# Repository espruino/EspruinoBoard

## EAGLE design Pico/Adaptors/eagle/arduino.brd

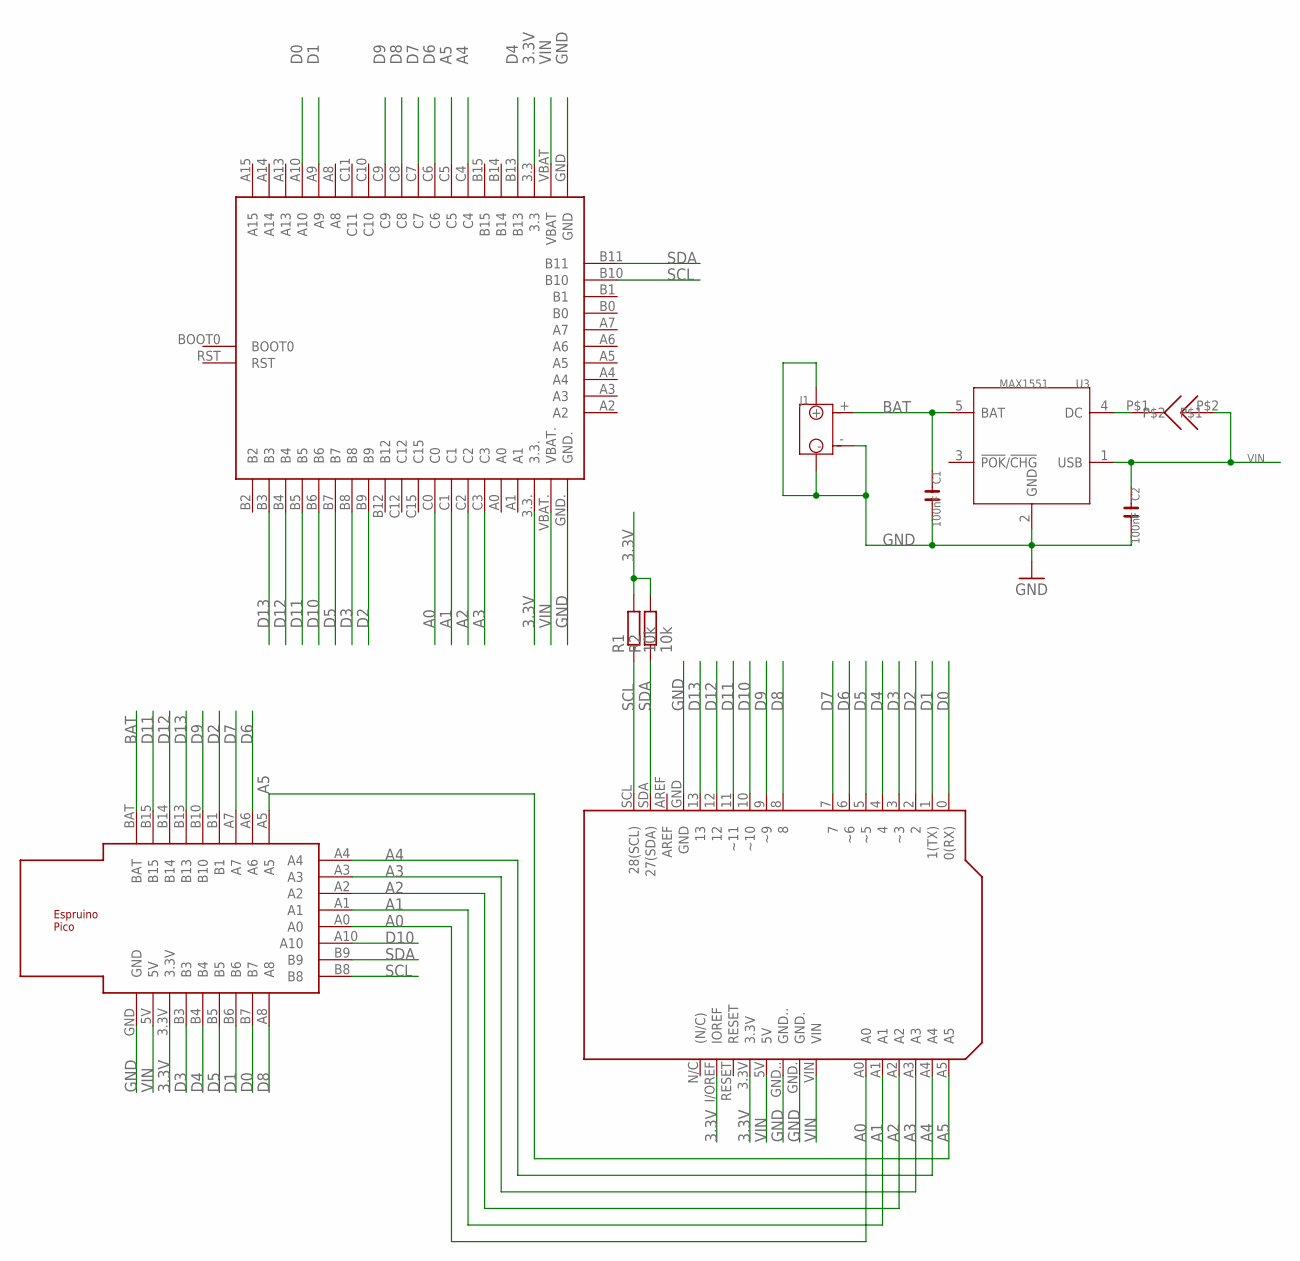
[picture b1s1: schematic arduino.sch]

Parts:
C1, C2: 100nF; C0603
J1: JST-2P-SMD-PW-3410050P1; 2P-SMD-2.0-90D
R1, R2: 10k; R0805
U3: MAX1551; SOT23-5
U$1: ESPRUINO_PICO_SMD
U$2: ARDUINO
U$3: ESPRUINO
U$4: SOLDERJUMPER

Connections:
3.3V: R1.2, R2.2, U$1.3.3V, U$2.3.3V, U$2.I/OREF (IOREF), U$3.3.3, U$3.3.3.
A0: U$1.A0, U$2.A0, U$3.C0
A1: U$1.A1, U$2.A1, U$3.C1
A2: U$1.A2, U$2.A2, U$3.C2
A3: U$1.A3, U$2.A3, U$3.C3
A4: U$1.A4, U$2.A4, U$3.C4
A5: U$1.A5, U$2.A5, U$3.C5
BAT: C1.1, J1.+, U3.5 (BAT), U$1.BAT
D0: U$1.B7, U$2.0 (0(RX)), U$3.A10
D1: U$1.B6, U$2.1 (1(TX)), U$3.A9
D2: U$1.B1, U$2.2, U$3.B9
D3: U$1.B3, U$2.3 (~3), U$3.B8
D4: U$1.B4, U$2.4, U$3.B13
D5: U$1.B5, U$2.5 (~5), U$3.B7
D6: U$1.A6, U$2.6 (~6), U$3.C6
D7: U$1.A7, U$2.7, U$3.C7
D8: U$1.A8, U$2.8, U$3.C8
D9: U$1.B10, U$2.9 (~9), U$3.C9
D10: U$1.A10, U$2.10 (~10), U$3.B6
D11: U$1.B15, U$2.11 (~11), U$3.B5
D12: U$1.B14, U$2.12, U$3.B4
D13: U$1.B13, U$2.13, U$3.B3
GND: C1.2, C2.2, J1.3, J1.4, J1.-, U3.2 (GND), U$1.GND, U$2.GND, U$2.GND., U$2.GND.., U$3.GND, U$3.GND.
unnamed: U3.4 (DC), U$4.P$1
SCL: R1.1, U$1.B8, U$2.SCL (28(SCL)), U$3.B10
SDA: R2.1, U$1.B9, U$2.SDA (27(SDA)), U$3.B11
VIN: C2.1, U3.1 (USB), U$1.5V, U$2.5V, U$2.VIN, U$3.VBAT, U$3.VBAT., U$4.P$2

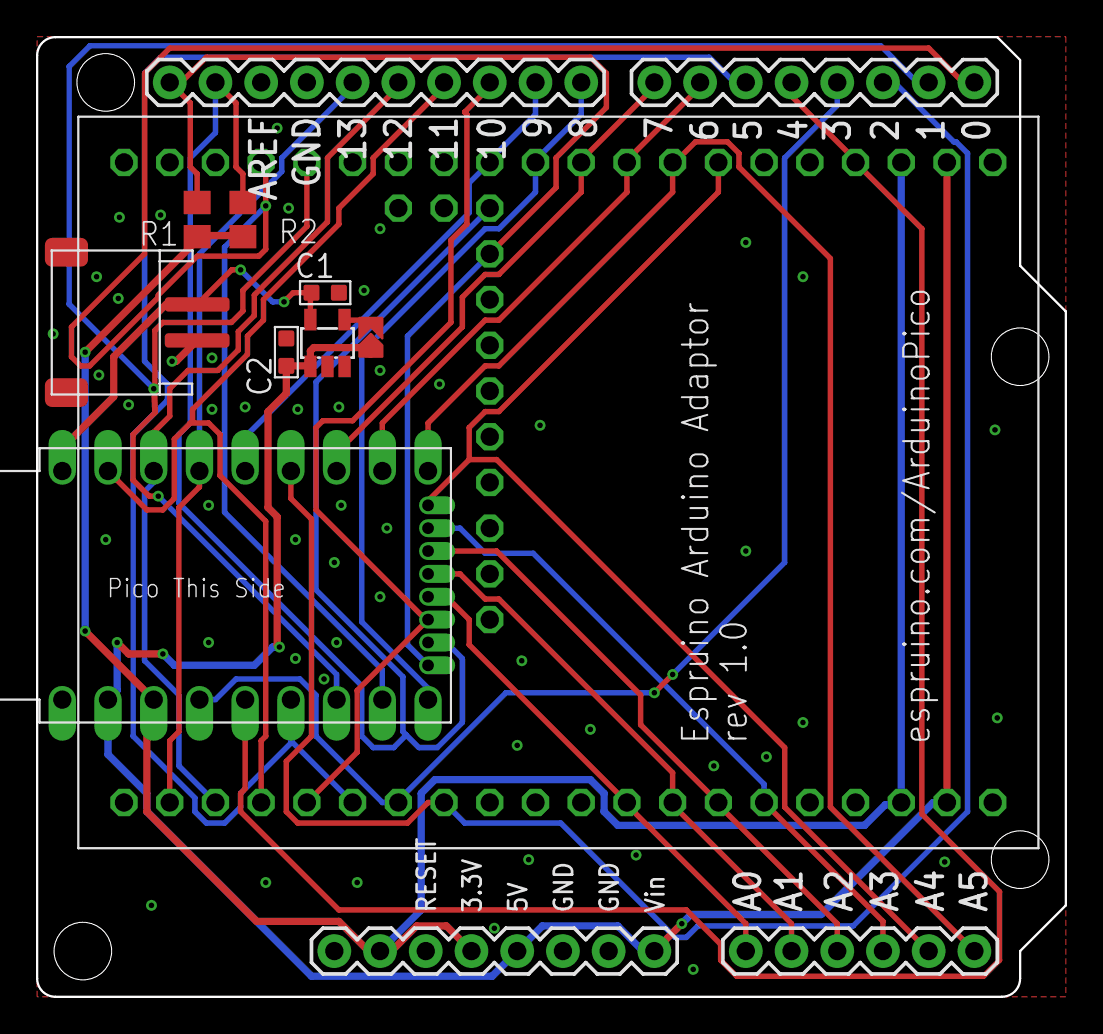
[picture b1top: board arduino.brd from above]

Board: 2 copper layers, 57.1 x 53.3 mm, 10 parts (0 on the bottom side), 27 nets.

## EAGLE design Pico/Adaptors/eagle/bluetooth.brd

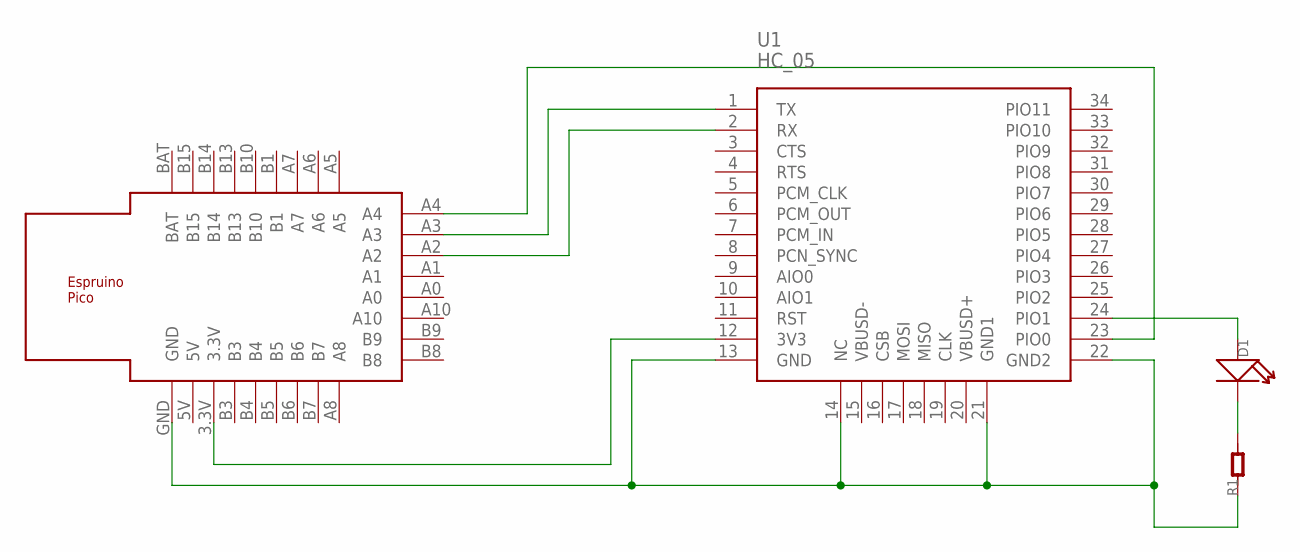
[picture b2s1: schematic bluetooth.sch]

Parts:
D1: LED; LED0603
R1: R-0603; R0603
U1: HC_05; BLUETOOTH_SMD
U$1: ESPRUINO_PICO_SMDONLY

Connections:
unnamed: U1.12 (3V3), U$1.3.3V
unnamed: R1.1, U1.13 (GND), U1.14 (NC), U1.21 (GND1), U1.22 (GND2), U$1.GND
unnamed: U1.1 (TX), U$1.A3
unnamed: U1.2 (RX), U$1.A2
unnamed: U1.23 (PIO0), U$1.A4
unnamed: D1.+, U1.24 (PIO1)
unnamed: D1.-, R1.2

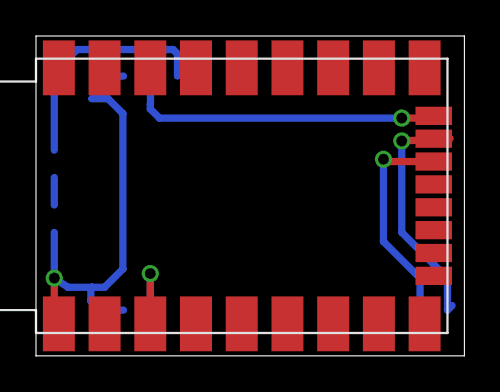
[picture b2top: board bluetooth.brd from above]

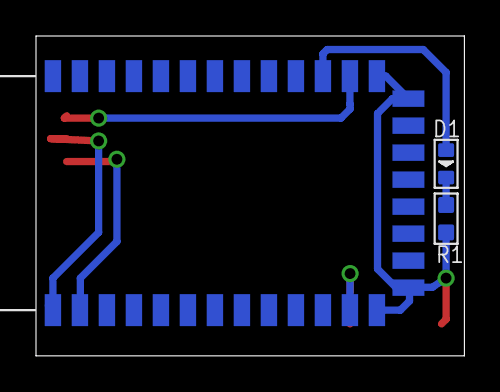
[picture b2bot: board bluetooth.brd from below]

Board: 2 copper layers, 23.8 x 17.8 mm, 4 parts (3 on the bottom side), 7 nets.

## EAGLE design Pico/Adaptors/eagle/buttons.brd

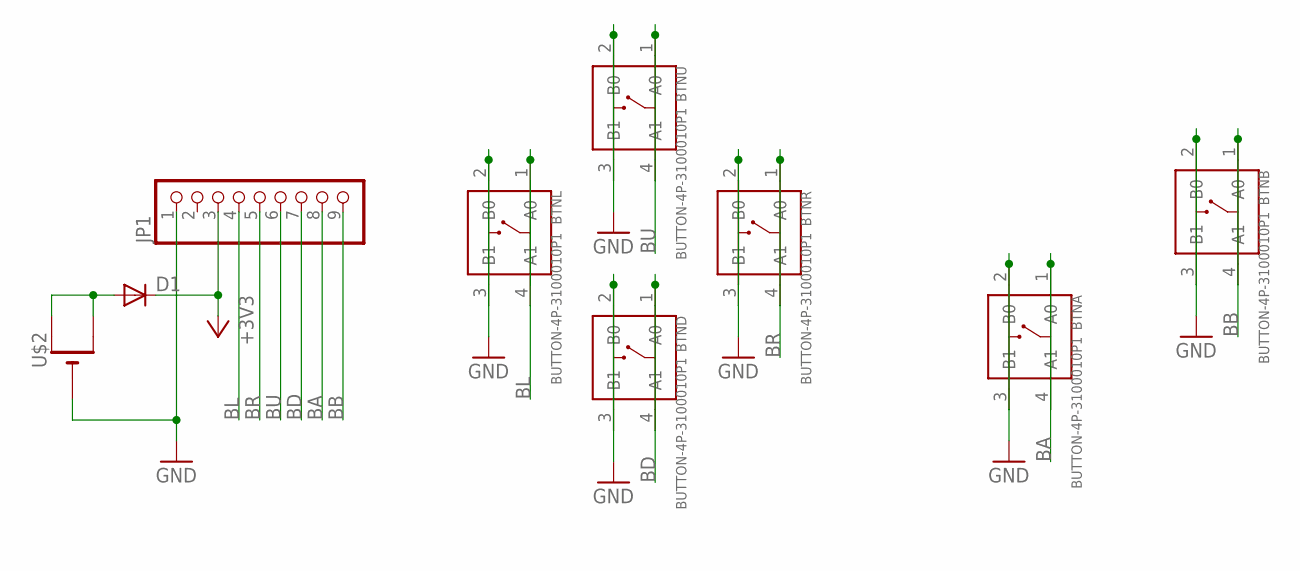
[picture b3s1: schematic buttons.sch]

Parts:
BTNA: BUTTON-4P-3100010P1; 4P-SMD-6.0X6.0X5.0H
BTNB: BUTTON-4P-3100010P1; 4P-SMD-6.0X6.0X5.0H
BTND: BUTTON-4P-3100010P1; 4P-SMD-6.0X6.0X5.0H
BTNL: BUTTON-4P-3100010P1; 4P-SMD-6.0X6.0X5.0H
BTNR: BUTTON-4P-3100010P1; 4P-SMD-6.0X6.0X5.0H
BTNU: BUTTON-4P-3100010P1; 4P-SMD-6.0X6.0X5.0H
D1: DIODE-SOD323-W; SOD323-W
JP1: PINHD-1X9; 1X09
U$2: CR2032SMT; CR2032-SMD

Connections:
+3V3: D1.C, JP1.3
BA: BTNA.1 (A0), BTNA.4 (A1), JP1.8
BB: BTNB.1 (A0), BTNB.4 (A1), JP1.9
BD: BTND.1 (A0), BTND.4 (A1), JP1.7
BL: BTNL.1 (A0), BTNL.4 (A1), JP1.4
BR: BTNR.1 (A0), BTNR.4 (A1), JP1.5
BU: BTNU.1 (A0), BTNU.4 (A1), JP1.6
GND: BTNA.2 (B0), BTNA.3 (B1), BTNB.2 (B0), BTNB.3 (B1), BTND.2 (B0), BTND.3 (B1), BTNL.2 (B0), BTNL.3 (B1), BTNR.2 (B0), BTNR.3 (B1), BTNU.2 (B0), BTNU.3 (B1), JP1.1, U$2.-
unnamed: D1.A, U$2.+$1 (+), U$2.+$2 (+1)

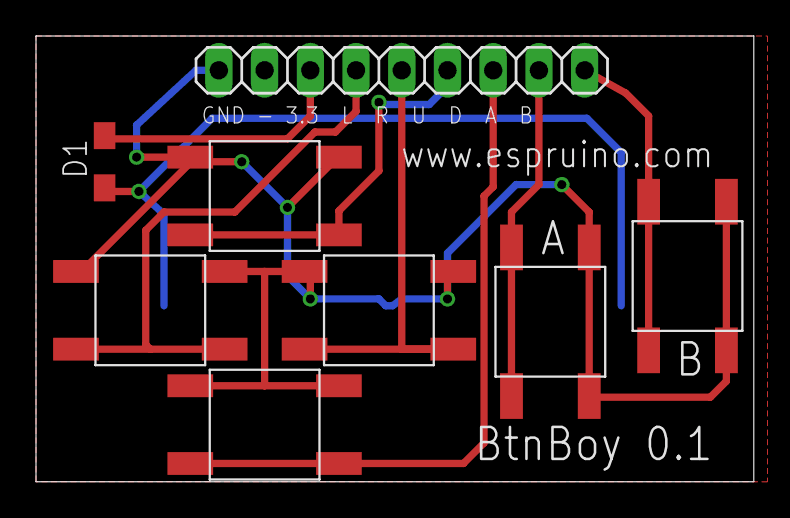
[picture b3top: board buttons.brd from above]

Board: 2 copper layers, 39.9 x 24.8 mm, 9 parts (1 on the bottom side), 9 nets.

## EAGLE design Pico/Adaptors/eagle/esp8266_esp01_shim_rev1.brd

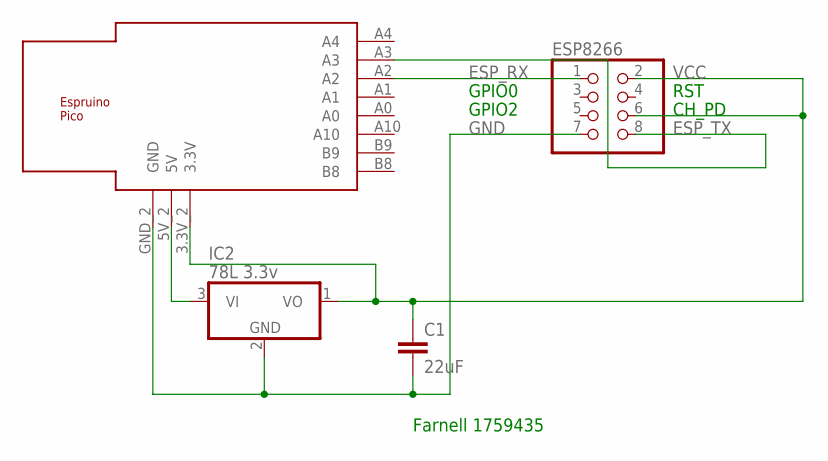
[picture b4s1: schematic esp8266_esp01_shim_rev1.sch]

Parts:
C1: 22uF; C1210
ESP8266: PINHD-2X4; 2X04
IC2: 78L 3.3v; TO92
U$1: ESPRUINO_PICO_0.05

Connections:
ESP_RX: ESP8266.1, U$1.A2
ESP_TX: ESP8266.8, U$1.A3
GND: C1.2, ESP8266.7, IC2.2 (GND), U$1.GND_2 (GND)
unnamed: IC2.3 (VI), U$1.5V_2 (5V)
VCC: C1.1, ESP8266.2, ESP8266.6, IC2.1 (VO), U$1.3.3V_2 (3.3V)

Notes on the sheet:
CH_PD
RST
GPIO0
GPIO2
Farnell 1759435

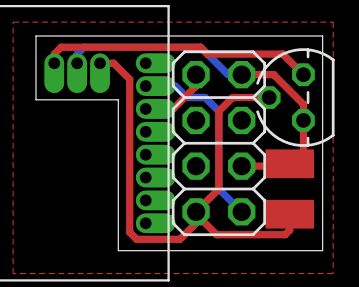
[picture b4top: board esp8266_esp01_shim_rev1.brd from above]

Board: 2 copper layers, 15.9 x 11.9 mm, 4 parts (0 on the bottom side), 5 nets.

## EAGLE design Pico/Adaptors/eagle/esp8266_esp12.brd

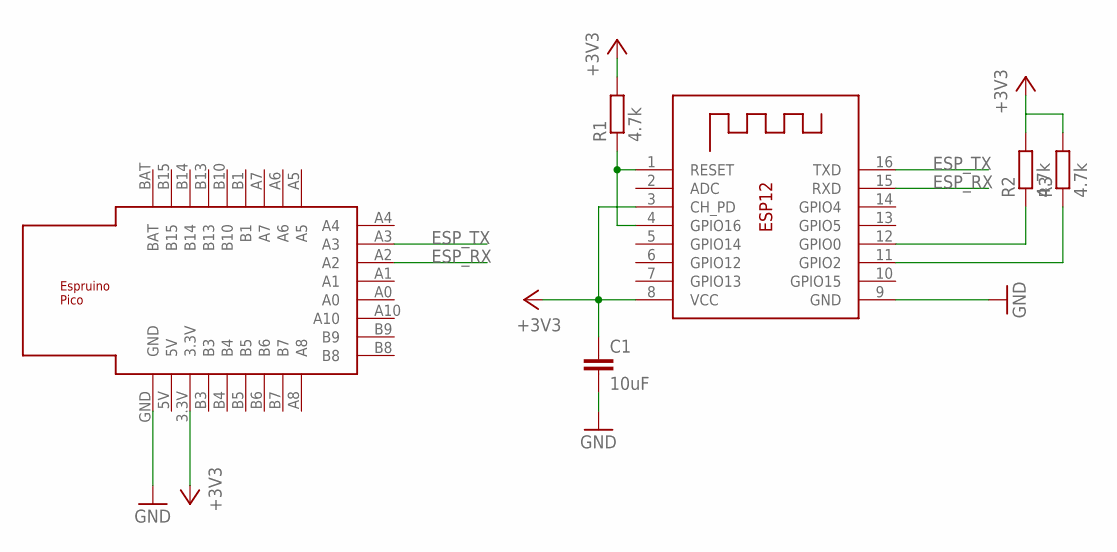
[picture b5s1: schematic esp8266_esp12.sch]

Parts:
C1: 10uF; C1206
R1, R2, R3: 4.7k; R1206
U$1: ESPRUINO_PICO_HALFSMD
X1: ESP-12

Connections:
+3V3: C1.1, R1.2, R2.2, R3.2, U$1.3.3V, X1.3 (CH_PD), X1.8 (VCC)
ESP_RX: U$1.A2, X1.15 (RXD)
ESP_TX: U$1.A3, X1.16 (TXD)
GND: C1.2, U$1.GND, X1.9 (GND)
unnamed: R3.1, X1.11 (GPIO2)
unnamed: R2.1, X1.12 (GPIO0)
unnamed: R1.1, X1.1 (RESET), X1.4 (GPIO16)

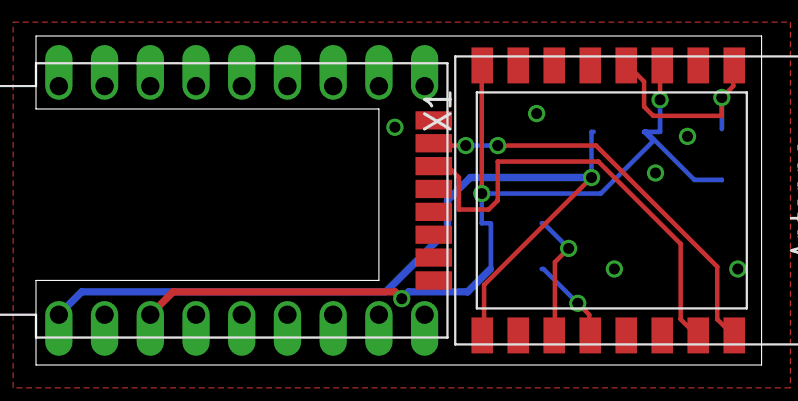
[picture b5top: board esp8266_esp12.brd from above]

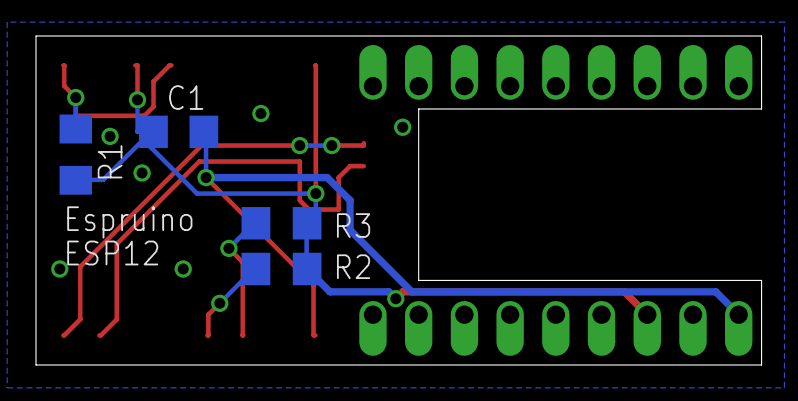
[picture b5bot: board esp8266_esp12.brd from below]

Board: 2 copper layers, 40.3 x 18.3 mm, 6 parts (4 on the bottom side), 7 nets.
